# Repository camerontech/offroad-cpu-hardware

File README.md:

# Cameron Tech Offroad CPU

Here is the Eagle schematic and board layout for the CTAIM1. Software can be found here: https://github.com/camerontech/offroad-cpu

If picking up and assembling all of these parts yourself is a bit daunting, you can purchase a kit or pre-assembled
unit here: http://store.camerontech.io/products/offroad-cpu

## Parts

**1 x ATMEGA328P-PU** [ATMEGA 328](http://amzn.to/2iHWBoK)

**1 x LCD** [SparkFun LCD-00709](https://www.sparkfun.com/products/709)

**1 x Multi-sensor** [10DOF Board](https://www.amazon.com/SUNKEE-1232055-Attitude-Indicator-L3G4200D/dp/B00CD239UG)

**1 x 5v Regulator** [Digikey MC7805CT-BPMS-ND]( http://www.digikey.com/product-search/en?WT.z_header=search_go&lang=en&site=us&keywords=mc7805ct-bpms-nd&x=-1136&y=-51&formaction=on)

**1 x 16MHz Clock Crystal** [Mouser 815-ABL-16-B2](http://www.mouser.com/Search/ProductDetail.aspx?R=ABL-16.000MHZ-B2virtualkey52750000virtualkey815-ABL-16-B2)

**1 x 10kΩ Potentiometer** [Digikey D4AA14-ND](http://www.digikey.com/product-search/en?WT.z_header=search_go&lang=en&site=us&keywords=D4AA14-ND&x=-1136&y=-51&formaction=on)

**2 x 10µF Capacitor** [Digikey P975-ND](http://www.digikey.com/product-search/en/capacitors/aluminum-capacitors/131081?k=p975-ND)

**1 x 0.1F Capacitor** [Digikey 399-4266-ND](http://www.digikey.com/product-search/en?WT.z_header=search_go&lang=en&site=us&keywords=399-4266-ND&x=-1151&y=-51&formaction=on)

**2 x 22pF Capacitor** [Digikey 399-9723-ND](http://www.digikey.com/product-detail/en/C315C220K5G5TA/399-9723-ND/3726119)

**1 x NPN Transistor** [Mouser 512-2N3904BU](http://www.mouser.com/Search/ProductDetail.aspx?R=2N3904BUvirtualkey51210000virtualkey512-2N3904BU)

**1 x 40-pin Straight Header** [SparkFun PRT-00116](https://www.sparkfun.com/products/116)

**1 x 40-pin Right-angle Header** [SparkFun PRT-00553](https://www.sparkfun.com/products/553)

**1 x Three-way switch** [Three-way Rocker Switch](https://www.sparkfun.com/products/8184)

**1 x Three-way switch breakout board** [Breakout Board](https://oshpark.com/shared_projects/Y3Nexyzu)

That'll get you everything you need to get it working. You'll still need to connect the three-way switch to the board
somehow and get power in. 

A 4-wire JST connector hooks up the three-way switch to the circuit and also lets you disconnect it:

**1 x 4-pin JST Connector** [SparkFun PRT-09916](https://www.sparkfun.com/products/9916)

You can solder 12v right to your circuit, or use a 9v battery. If you want something less permanent then use a screw
terminal so you can unhook the wires again if necessary:

**1 x 2-pin screw terminal** [SparkFun PRT-08432](https://www.sparkfun.com/products/8432)

**1 x 9v Battery Strap** [Digikey 81-8K-ND](http://www.digikey.com/product-detail/en/81-8/81-8K-ND/303954)

Finally, unless you want to do a lot of wire-routing and excess soldering by hand and manually following the 
schematic to hook everything up, you can also get the circuit board that lays everything out nicely and attaches 
as a backpack to the LCD screen:

**1 x Offroad CPU Circuit Board** [Cameron Tech CTORD100](https://oshpark.com/shared_projects/I7EZdFw5)

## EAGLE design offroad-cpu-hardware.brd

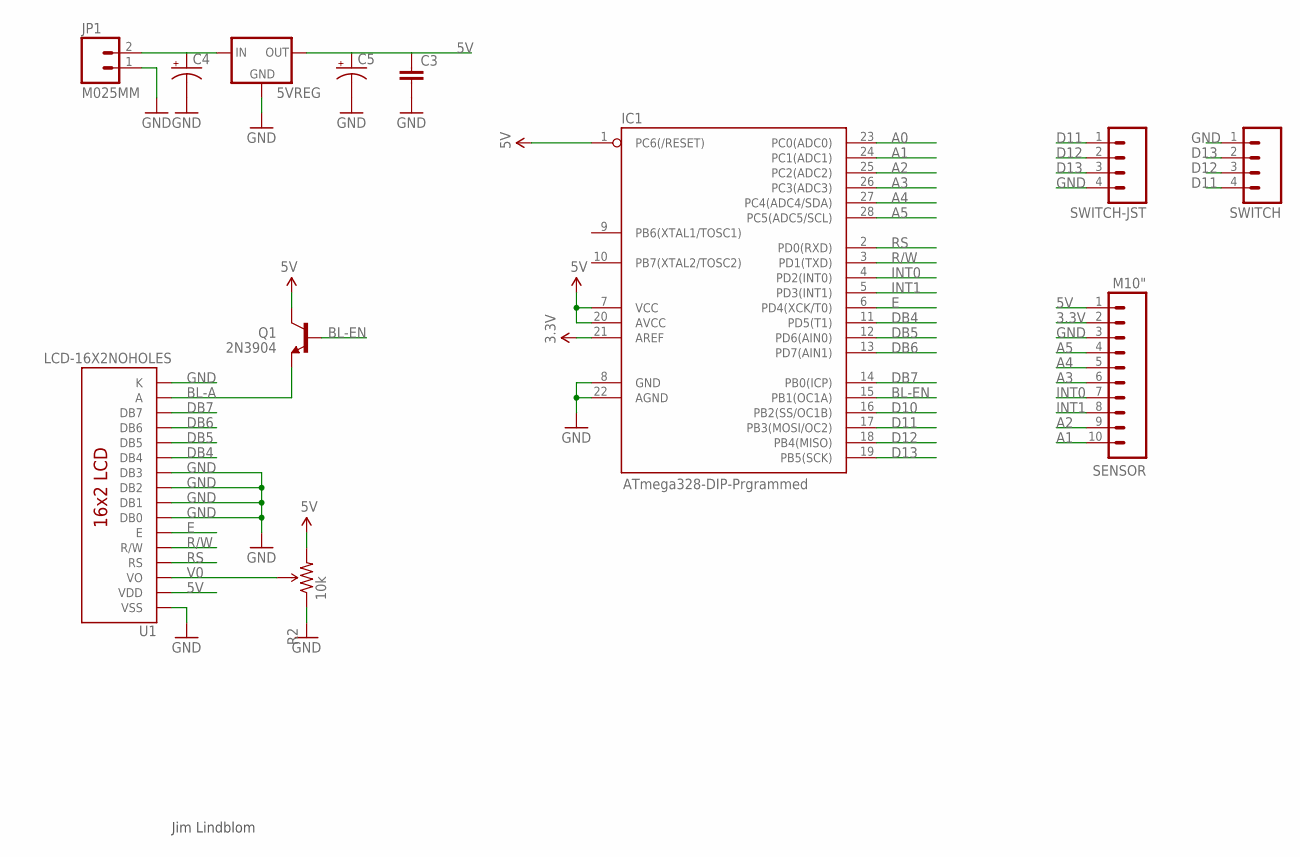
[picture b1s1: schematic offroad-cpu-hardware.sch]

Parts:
5VREG: 78XXS
C3: CAPPTH2; CAP-PTH-SMALL2
C4, C5: CAP_POLPTH2; CPOL-RADIAL-10UF-25V
IC1: ATmega328-DIP-Prgrammed; DIL28-3
JP1: M025MM; SCREWTERMINAL-5MM-2
Q1: 2N3904; TO-92
R2: 10k; TRIM_POT_PTH
SENSOR: M10"; 1X10
SWITCH: M04PTH; 1X04
SWITCH-JST: M04JST-PTH; JST-4-PTH
U1: LCD-16X2NOHOLES; LCD-16X2_NOHOLES

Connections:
3.3V: IC1.21 (AREF), SENSOR.2
5V: 5VREG.OUT, C3.1, C5.1 (+), IC1.1 (PC6(/RESET)), IC1.7 (VCC), IC1.20 (AVCC), Q1.3 (C), R2.3 (CW), SENSOR.1, U1.2 (VDD)
A0: IC1.23 (PC0(ADC0))
A1: IC1.24 (PC1(ADC1)), SENSOR.10
A2: IC1.25 (PC2(ADC2)), SENSOR.9
A3: IC1.26 (PC3(ADC3)), SENSOR.6
A4: IC1.27 (PC4(ADC4/SDA)), SENSOR.5
A5: IC1.28 (PC5(ADC5/SCL)), SENSOR.4
BL-A: Q1.1 (E), U1.15 (A)
BL-EN: IC1.15 (PB1(OC1A)), Q1.2 (B)
D10: IC1.16 (PB2(SS/OC1B))
D11: IC1.17 (PB3(MOSI/OC2)), SWITCH.4, SWITCH-JST.1
D12: IC1.18 (PB4(MISO)), SWITCH.3, SWITCH-JST.2
D13: IC1.19 (PB5(SCK)), SWITCH.2, SWITCH-JST.3
DB4: IC1.11 (PD5(T1)), U1.11 (DB4)
DB5: IC1.12 (PD6(AIN0)), U1.12 (DB5)
DB6: IC1.13 (PD7(AIN1)), U1.13 (DB6)
DB7: IC1.14 (PB0(ICP)), U1.14 (DB7)
E: IC1.6 (PD4(XCK/T0)), U1.6 (E)
GND: 5VREG.GND, C3.2, C4.2 (-), C5.2 (-), IC1.8 (GND), IC1.22 (AGND), JP1.1, R2.1 (CCW), SENSOR.3, SWITCH.1, SWITCH-JST.4, U1.1 (VSS), U1.7 (DB0), U1.8 (DB1), U1.9 (DB2), U1.10 (DB3), U1.16 (K)
INT0: IC1.4 (PD2(INT0)), SENSOR.7
INT1: IC1.5 (PD3(INT1)), SENSOR.8
R/W: IC1.3 (PD1(TXD)), U1.5 (R/W)
RS: IC1.2 (PD0(RXD)), U1.4 (RS)
V0: R2.2 (WIPER), U1.3 (VO)
VCC: 5VREG.IN, C4.1 (+), JP1.2

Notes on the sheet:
Jim Lindblom

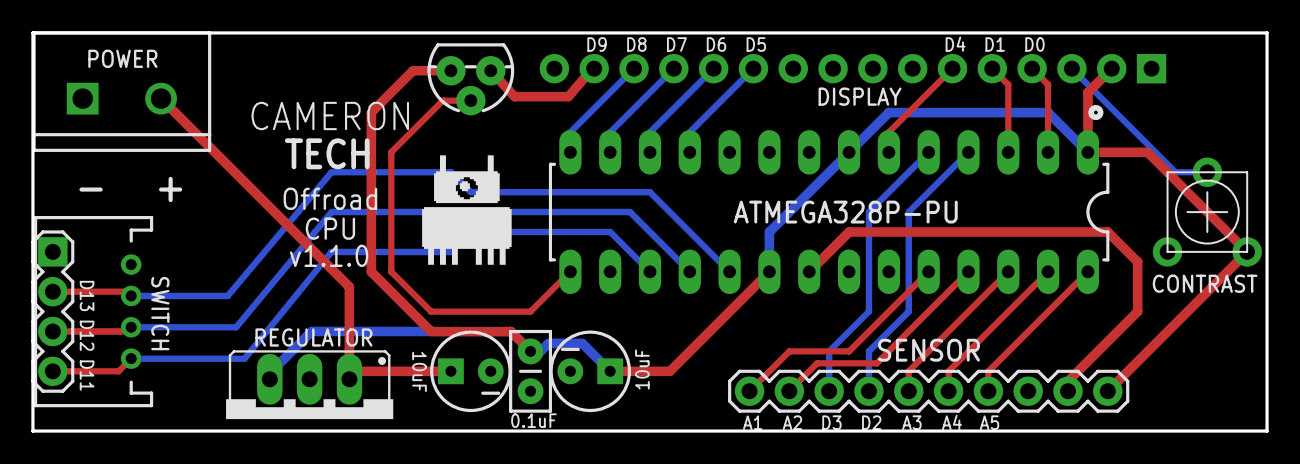
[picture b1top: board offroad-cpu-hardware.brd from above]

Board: 2 copper layers, 78.7 x 25.4 mm, 12 parts (1 on the bottom side), 24 nets.

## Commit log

2013-09-24 Added parts list to README
2013-09-24 Create gh-pages branch via GitHub
2013-09-25 Moved pins away from bottom edge, updated silkscreen
2013-10-06 Changes 3-way switch from 5V to GND, beefs up power connections to 0.016 wire width
2013-10-06 Adds version file
2013-10-09 Removes extra voltage smoothing caps (dual regulator board is doing this already)
2013-10-09 Bumps version to 0.2.0 (pre-release)
2013-10-09 Bumps to 0.3.0
2013-10-09 Updates backside label of barometer SDA pin, moves branding
2013-10-14 Switches to 10DOF board from Sunkee
    http://www.amazon.com/gp/product/B00CD239UG/ref=oh_details_o01_s00_i00?ie=UTF8&psc=1
2013-10-14 Adds screw terminals, connects currently unused pins
2013-10-14 Nudged a wire out of the way of a couple pads
2013-10-17 Bumped to 1.0.0, off to the fabricator!
2013-10-20 New parts list
2013-11-13 Updates parts list
2013-11-13 Added headers to parts list
2013-11-13 Updated with Cameron Tech ATMEGA (pre-bootloaded)
2013-11-14 Moves ATMEGA a tad so it's easier to remove, updates silkscreens on some pins
2013-11-14 Adds schematic image
2013-11-14 Adds schematic
2013-11-14 Renamed files to match repo
2013-11-15 New sensor link
2014-01-06 Fixes nav switch wiring running into timer pads
2015-02-26 Removes timing crystal and associated capacitors
    http://arduino.cc/en/Tutorial/ArduinoToBreadboard
2015-02-26 Updates version to 1.1.0
2017-11-08 Update README with non-CT links
2019-07-08 Updated link to 10DOF board

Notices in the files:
parts and their libraries:
SparkFun-Connectors: Licensing: CC v3.0 Share-Alike You are welcome to use this library for commercial purposes.
